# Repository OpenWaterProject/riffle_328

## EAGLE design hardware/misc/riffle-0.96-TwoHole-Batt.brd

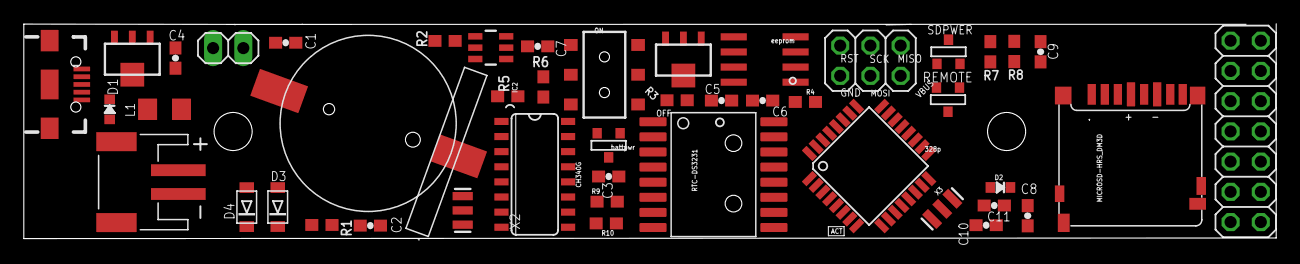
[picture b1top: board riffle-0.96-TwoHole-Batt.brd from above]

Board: 2 copper layers, 105.2 x 18.2 mm, 47 parts (1 on the bottom side), 48 nets, no tracks yet.

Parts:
BAT: CR1220; BATTCON_12MM_SMT
BATTPOWER: FDN340P; SOT-23
C1, C4, C5, C6: 10uF; 0603-CAP
C2, C3, C7, C8, C9, C10, C11: 0.1uF; 0603-CAP
CN1: JST-PH-2-SMT-RA
D1, D2: LED0603; 0603-LED
D3, D4: SCHOTTKY; SOD-123FL
IC1: ATMEGA328P; TQFP32-08
IC2: MCP73831; SOT23-5
IC3: CH340G; SO16
IC4, IC6: MCP1700-33; SOT89
IC5: 24AA128SN; SO-08
ISP: 2X03
J1: AYZ0202
JP1: 1X02
JP3: 1X04-SMD
JP5: 2X07
L1: 500mA; R1206
R1, R3, R4, R5, R6, R9, R10: 10K; 0603-NO
R2: 4.7K; 0603-NO
R7, R8: 50K; 0603-NO
REMOTE: FDN340P; SOT-23
RTC-DS3231: DS3231
SDPWER: FDN340P; SOT-23
U$1: MICROSD-HRS_DM3D; DM3D
U$4: USB-AB-MICRO-SMD_V02_BOSS
X2: 12MHz; RESONATOR-SMD
X3: 16 MHz; RESONATOR-SMD

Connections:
A0: IC1.23, JP5.13
A1: IC1.24, JP3.1
A2: IC1.25, JP3.2
A3: IC1.26, R5.2, R6.1
AREF: C10.1, IC1.20
D2: IC1.32, JP5.7
D3: IC1.1, JP5.5
D4: BATTPOWER.3, IC1.2
D5: IC1.9, JP3.4
D6: IC1.10, SDPWER.3
D7: IC1.11, U$1.CD/DAT3
D8: IC1.12, REMOTE.3
D9: IC1.13, R4.2
D10: IC1.14, JP5.2
D+: IC3.5, U$4.D+1
D-: IC3.6, U$4.D-1
GND: BAT.P$1, C1.1, C2.2, C4.2, C5.2, C6.2, C7.1, C8.2, C9.1, C10.2, C11.1, CN1.2, D2.MINUS, IC1.3, IC1.5, IC1.21, IC2.2, IC3.1, IC4.1, IC5.1, IC5.2, IC5.3, IC5.4, IC5.7, IC6.1, ISP.6, JP1.1, JP3.3, JP5.1, R2.1, R5.1, RTC-DS3231.5, RTC-DS3231.6, RTC-DS3231.7, RTC-DS3231.8, RTC-DS3231.9, RTC-DS3231.10, RTC-DS3231.11, RTC-DS3231.12, RTC-DS3231.13, U$1.GND1, U$1.GND2, U$1.GND3, U$1.GND4, U$1.SW_A, U$1.SW_B, U$1.VSS, U$4.GND1, X2.2, X3.2
MISO: IC1.16, ISP.1, JP5.4, U$1.DAT0
MOSI: IC1.15, ISP.4, JP5.6, U$1.CMD
unnamed: D1.PLUS, R1.1
unnamed: IC1.7, X3.1
unnamed: IC1.8, X3.3
unnamed: C9.2, R7.1, R8.2, SDPWER.1, U$1.VDD
unnamed: D1.MINUS, IC2.1
unnamed: IC2.5, R2.2
unnamed: C8.1, JP5.3, REMOTE.1
unnamed: C2.1, IC3.4, IC3.16, IC6.3
unnamed: D3.A, L1.2
unnamed: IC3.7, X2.1
unnamed: IC3.8, X2.3
unnamed: D4.A, JP1.2
unnamed: BATTPOWER.1, C7.2, R6.2
unnamed: R7.2, U$1.DAT1
unnamed: D2.PLUS, R4.1
unnamed: R8.1, U$1.DAT2
unnamed: L1.1, U$4.VBUS1
RESET: C3.1, IC1.29, ISP.5, R3.1
RST: C3.2, IC3.14
RTC_BATT: BAT.P$2, RTC-DS3231.14
RXD: IC1.30, IC3.2, JP5.10
SCK: IC1.17, ISP.3, JP5.8, U$1.CLK
SCL: IC1.28, IC5.6, JP5.11, R9.1, RTC-DS3231.16
SDA: IC1.27, IC5.5, JP5.9, R10.1, RTC-DS3231.15
TXD: IC1.31, IC3.3, JP5.12
VBAT: BATTPOWER.2, CN1.1, D4.C, IC2.3, J1.2, JP5.14
VBUS: C1.2, C4.1, D3.C, IC2.4, IC6.2, ISP.2, R1.2
VCC: C6.1, C11.2, IC1.4, IC1.6, IC1.18, IC4.3, IC5.8, R3.2, R9.2, R10.2, REMOTE.2, RTC-DS3231.2, SDPWER.2
VDD: C5.1, IC4.2, J1.1

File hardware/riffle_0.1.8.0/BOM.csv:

Part,Details,Device,Package,Description,,MF,Cost per 100,cost,Source
BAT,CR1220,BATTERYBATTERY_12MM_SMT,BATTCON_12MM_SMT,Battery Holders,,,1.8,1.8,http://www.digikey.com/product-detail/en/1056TR/1056KCT-ND/4772075
"BATTPOWER, REMOTE, SDPWER",FDN340P,PMOSSOT23,SOT-23,MOS FET,,,0.24,0.72,http://www.digikey.com/product-detail/en/FDN340P/FDN340PCT-N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
"C1,C4,C5,C6",10uF,CAP0603-CAP,0603-CAP,Capacitor,*,,0.07,0.28,http://www.digikey.com/product-detail/en/CC0603MRX5R5BB106/3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
"C2,C3,C7,C8,C9,C10,C11",0.1uF,CAP0603-CAP,0603-CAP,Capacitor,*,,0.04,0.28,http://www.digikey.com/product-detail/en/C0603C104J4RACTU/39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
CN1,,JST_2PIN-SMT-RA,JST-PH-2-SMT-RA,JST 2-Pin Connectors of various flavors,,,0.4,0.4,http://www.digikey.com/product-detail/en/S2B-PH-SM4-TB%28LF%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
D1,LED0603,LED0603,0603-LED,,*,blue,0.23,0.23,http://www.digikey.com/product-detail/en/APT1608QBC%2FD/754-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
D2,LED0603,LED0603,0603-LED,,,yellow,0.17,0.17,http://www.digikey.com/product-detail/en/APT1608SYCK/754-112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
"D3, D4",SCHOTTKY,DIODE_SOD-123FL,SOD-123FL,Diode,,,0.22,0.44,http://www.digikey.com/product-detail/en/SM4002PL-TP/SM4002P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
IC1,ATMEGA328P,MEGA8-AI,TQFP32-08,MICROCONTROLLER,*,ATMEGA8-16AU,2.7,2.7,http://www.digikey.com/product-detail/en/ATMEGA328P-AU/ATMEG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
IC2,MCP73831,MCP73831,SOT23-5,Microchip's MCP73831,,,0.42,0.42,http://www.digikey.com/product-detail/en/MCP73831T-2ACI%2FOT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
IC3,CH340G,CH340G,SO16,,,,0.6,0.6,rui
"IC4, IC6",MCP1700-33,MCP1700SOT89,SOT89,VOLTAGE REGULATOR,*,,0.29,0.58,http://www.digikey.com/product-detail/en/0/MCP1700T3302EMBCT-ND
IC5,24AA128SN,24AA128SN,SO-08,Serial EEPROM,,24AA128-I/SN,0.5,0.5,http://www.digikey.com/product-detail/en/24AA128-I%2FSN/24AA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
ISP,,PINHD-2X3,2X03,PIN HEADER,,,,,(leave open for programming)
J1,AYZ0202,AYZ0202,AYZ0202,SPDT Slide Switch,,,1.07,1.07,http://www.digikey.com/product-detail/en/AYZ0202AGRLC/401-20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
JP1,,PINHD-1X2,1X02,PIN HEADER,,,,,(leave open)
JP3,,M04SMD,1X04-SMD,Header 4,,,,,(leave open)
JP5,,PINHD-2X7,2X07,PIN HEADER,,,0.98,0.98,http://www.digikey.com/product-detail/en/PPTC072LJBN-RC/S552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
L1,500mA,PTCFUSE-1206,R1206,"PTC fuses, resettable thermistors",,,0.17,0.17,http://www.digikey.com/product-detail/en/0ZCA0050FF2G/507-14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
"R1,R3,R4,R5,R6,R9,R10",10K,RESISTOR_0603_NOOUT,0603-NO,Resistors,*,,0.02,0.14,http://www.digikey.com/product-detail/en/CR0603-JW-103GLF/CR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
R2,4.7K,RESISTOR_0603_NOOUT,0603-NO,Resistors,*,,0.11,0.11,http://www.digikey.com/product-detail/en/MCT0603MD4701DP500/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
"R7,R8",50K,RESISTOR_0603_NOOUT,0603-NO,Resistors,*,,0.005,0.01,http://www.digikey.com/product-detail/en/RC0603JR-07100RL/31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
RTC-DS3231,DS3231,DS3231,DS3231,,,,6.3,6.3,http://www.digikey.com/product-detail/en/DS3231S%23/DS3231S%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
U$1,MICROSD-HRS_DM3D,MICROSD-HRS_DM3D,DM3D,,*,,1.5,1.5,http://www.digikey.com/product-detail/en/DM3D-SF/HR1941CT-ND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
U$4,,"USB-AB""",USB-AB-MICRO-SMD_V02_BOSS,This is a USB AB connector that is compatible with USB OTG. i.e. this connector can serve as a host or device,,,0.6,0.6,http://www.digikey.com/product-detail/en/10104111-0001LF/609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
X2,12MHz,RESONATORSMD,RESONATOR-SMD,Resonator,,X,0.4,0.4,https://www.digikey.com/product-detail/en/CSTCE12M0G55-R0/49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
X3,16 MHz,RESONATORSMD,RESONATOR-SMD,Resonator,*,,0.32,0.32,http://www.digikey.com/product-detail/en/CSTCE16M0V53-R0/490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

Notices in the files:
parts and their libraries:
microbuilder: This work is placed in the public domain, and may be freely used for commercial and non-commercial work with the following conditions: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
